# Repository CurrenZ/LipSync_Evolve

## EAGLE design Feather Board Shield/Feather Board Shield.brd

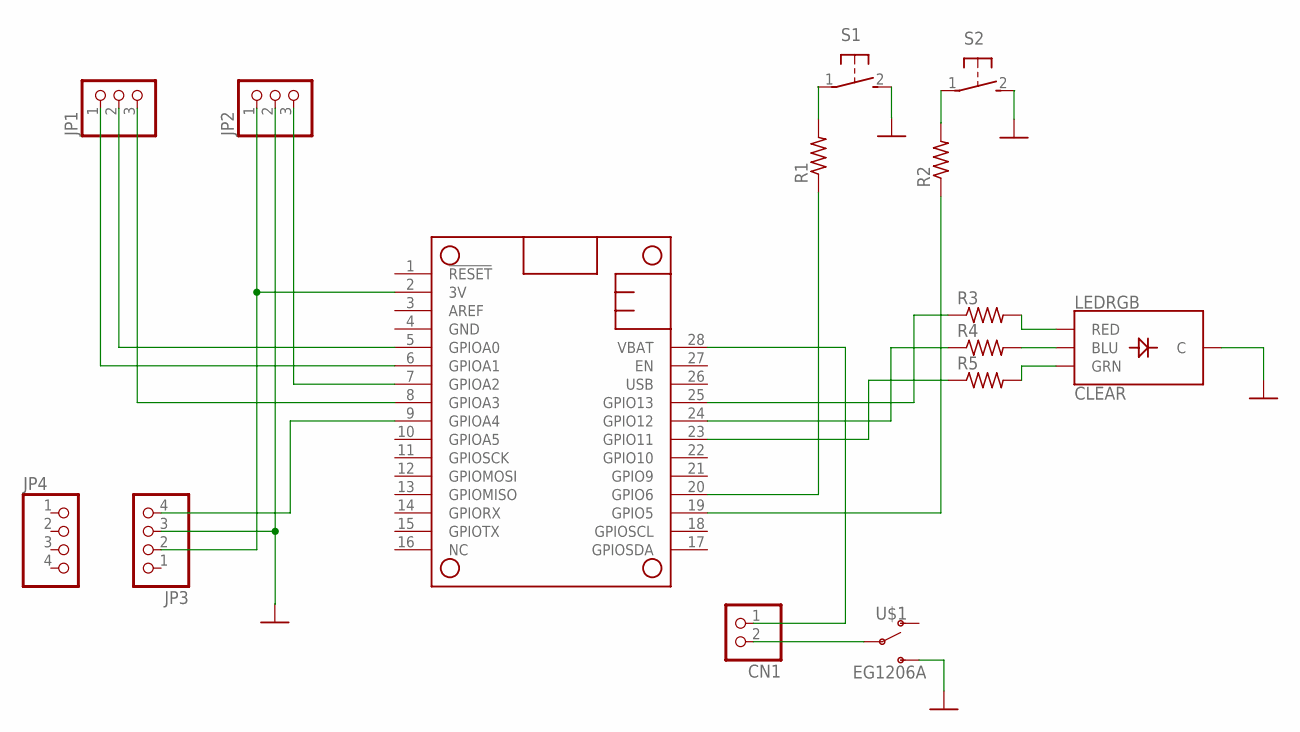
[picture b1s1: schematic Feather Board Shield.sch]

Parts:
CN1: ADAFRUIT_JST_2PIN-SMT-RA; ADAFRUIT_JST-PH-2-SMT-RA
JP1, JP2: PINHEAD_PINHD-1X3/90; PINHEAD_1X03/90
JP3, JP4: PINHEAD_PINHD-1X4; PINHEAD_1X04
LEDRGB: CLEAR; SPARKFUN-LED_LED-RGB-THRU
MS1: ADAFRUIT_FEATHERWING_NODIM; ADAFRUIT_FEATHERWING_DIM
R1, R2, R3, R4, R5: RESISTOR_R-US_0204/7; RESISTOR_0204/7
S1, S2: ADAFRUIT_31-XXSKINNY; ADAFRUIT_B3F-31XX-SKINNIER
U$1: EG1206A

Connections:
3V: JP2.1, JP3.2, MS1.2 (3V)
GND: JP2.2, JP3.3, LEDRGB.2 (C), MS1.4 (GND), S1.2 (S), S2.2 (S), U$1.3 (S)
unnamed: MS1.25 (GPIO13), R3.1
unnamed: MS1.24 (GPIO12), R4.1
unnamed: MS1.23 (GPIO11), R5.1
unnamed: LEDRGB.1 (RED), R3.2
unnamed: LEDRGB.4 (BLU), R4.2
unnamed: LEDRGB.3 (GRN), R5.2
unnamed: MS1.20 (GPIO6), R1.1
unnamed: MS1.19 (GPIO5), R2.1
unnamed: R1.2, S1.1
unnamed: R2.2, S2.1
unnamed: CN1.2 (1), U$1.2
unnamed: JP2.3, MS1.7 (GPIOA2)
unnamed: JP1.1, MS1.6 (GPIOA1)
unnamed: JP1.2, MS1.5 (GPIOA0)
unnamed: JP1.3, MS1.8 (GPIOA3)
unnamed: JP3.4, MS1.9 (GPIOA4)
VBAT: CN1.1 (2), MS1.28 (VBAT)

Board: 2 copper layers, 15 parts (5 on the bottom side), 19 nets, no tracks yet.

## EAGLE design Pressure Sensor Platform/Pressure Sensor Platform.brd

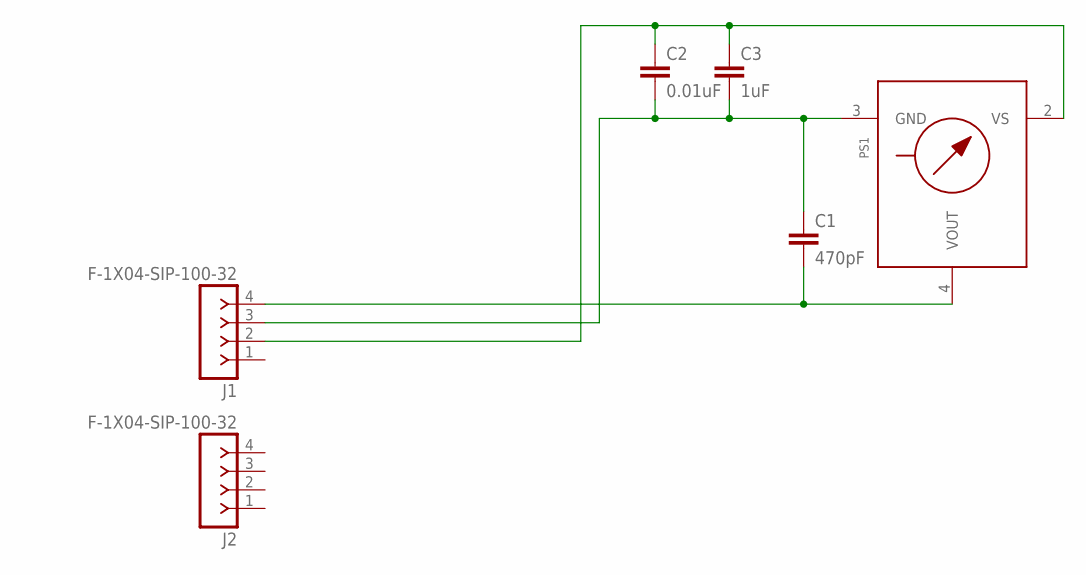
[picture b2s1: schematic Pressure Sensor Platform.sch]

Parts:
C1: 470pF; CAP-PTH-SMALL-KIT
C2: 0.01uF; CAP-PTH-SMALL-KIT
C3: 1uF; CAP-PTH-SMALL-KIT
J1, J2: F-1X04-SIP-100-32; SIP-100-04-32
PS1: MPX-1351; 1351

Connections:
COM: C2.1, C3.1, J1.2, PS1.2 (VS)
unnamed: C1.1, C2.2, C3.2, J1.3, PS1.3 (GND)
unnamed: C1.2, J1.4, PS1.4 (VOUT)

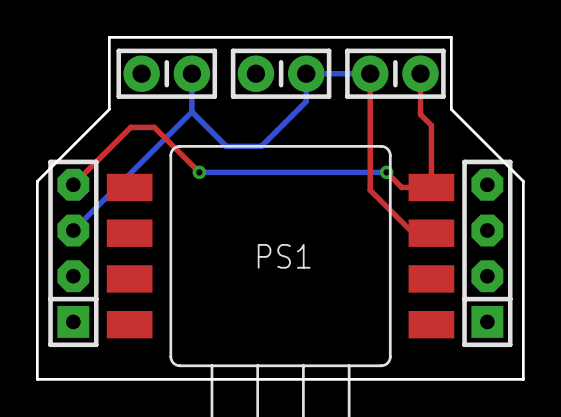
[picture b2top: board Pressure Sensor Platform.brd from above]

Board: 2 copper layers, 27.0 x 19.0 mm, 6 parts (0 on the bottom side), 3 nets.

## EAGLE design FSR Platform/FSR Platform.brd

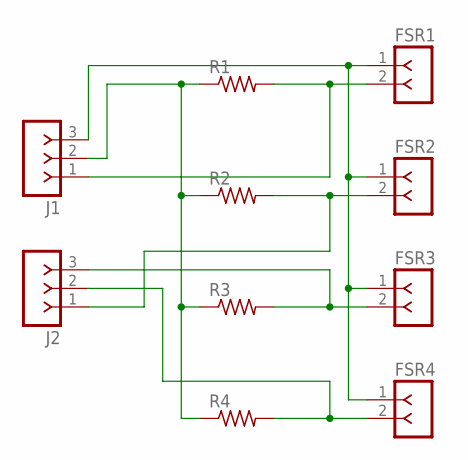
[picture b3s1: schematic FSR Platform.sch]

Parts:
FSR1, FSR2, FSR3, FSR4: FSR-5''
J1, J2: F-1X03-SIP-100-40; SIP-100-03-40
R1, R2, R3, R4: RESISTOR_R-US_0204/5; RESISTOR_0204/5

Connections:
COM0: J1.2, R1.1, R2.1, R3.1, R4.1
COM1: FSR1.1, FSR2.1, FSR3.1, FSR4.1, J1.3
unnamed: FSR1.2, J1.1, R1.2
unnamed: FSR2.2, J2.1, R2.2
unnamed: FSR3.2, J2.3, R3.2
unnamed: FSR4.2, J2.2, R4.2

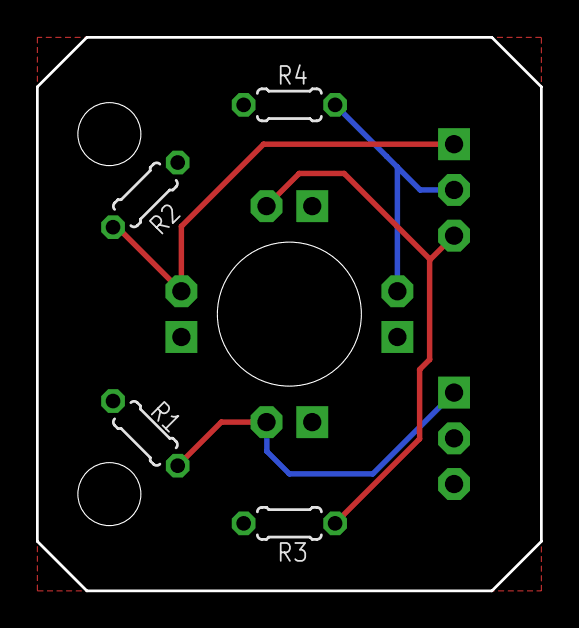
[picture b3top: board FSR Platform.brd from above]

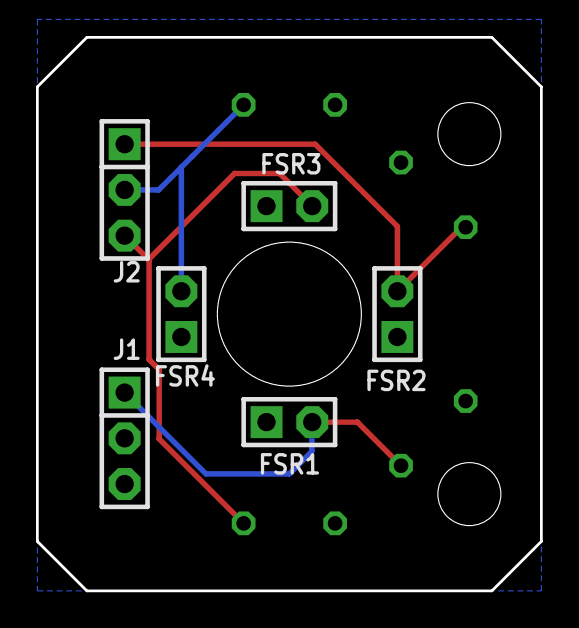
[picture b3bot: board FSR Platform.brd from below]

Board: 2 copper layers, 28.0 x 30.8 mm, 10 parts (6 on the bottom side), 6 nets.

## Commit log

2018-08-02 deleted unneeded files
